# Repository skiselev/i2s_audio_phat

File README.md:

# I2S Audio pHAT
I2S Audio Interface for Raspberry Pi Zero

## Introduction
This is a Raspberry Pi Zero pHAT form-factor I2S audio interface board based on a [Cirrus Logic (Wolfson) WM8731](https://www.cirrus.com/products/wm8731/) audio codec. It provides line input, line output, headphones output, and includes an on-board microphone.

## Hardware Documentation

### Schematic and PCB Layout

[Schematic - Version 3.0](documentation/I2S_Audio_pHAT-Schematic-3.0.pdf)

[PCB Layout - Version 3.0](documentation/I2S_Audio_pHAT-Board-3.0.pdf)

### Bill of Materials

[I2S Audio pHAT project on Mouser.com](https://www.mouser.com/ProjectManager/ProjectDetail.aspx?AccessID=6262cdf84a) - View and order all components except of the PCB.

[I2S Audio pHAT project on OSH Park](https://oshpark.com/shared_projects/yxrgLBxI) - View and order the PCB.

Component type     | Reference | Description                       | Quantity | Possible sources and notes 
------------------ | --------- | --------------------------------- | -------- | --------------------------
PCB                |           | I2S Audio pHAT PCB - Version 3.0  | 1        | Order from [OSH Park](https://oshpark.com/shared_projects/yxrgLBxI)
Integrated Circuit | U1        | WM8731, I2S audio codec, SSOP28   | 1        | Mouser [238-WM8731SEDS/V](https://www.mouser.com/ProductDetail/238-WM8731SEDS-V)
Integrated Circuit | U2        | TPS79333DBVR, LDO, SOT23-5        | 1        | Mouser [595-TPS79333DBVR](https://www.mouser.com/ProductDetail/595-TPS79333DBVR)
Integrated Circuit | U3        | CAT24C32WI-GT3, I2C EEPROM, SOIC8 | 1        | Mouser [698-CAT24C32WI-GT3](https://www.mouser.com/ProductDetail/698-CAT24C32WI-GT3)
Crystal            | X1        | 12.288MHz, 3 mm x 5.3 mm          | 1        | Mouser [717-7A-12.288MAAJ-T](https://www.mouser.com/ProductDetail/717-7A-12288MAAJ-T)
Microphone         | MK1       | 9.7 mm, electret condenser microphone | 1        | Mouser [490-CMA-4544PF-W](https://www.mouser.com/ProductDetail/490-CMA-4544PF-W)
Connector          | P1        | 3.5 mm audio jack, blue           | 1        | Mouser [806-STX-31205B284C](https://www.mouser.com/ProductDetail/806-STX-31205B284C)
Connector          | P2        | 3.5 mm audio jack, green          | 1        | Mouser [806-STX-31205B577C](https://www.mouser.com/ProductDetail/806-STX-31205B577C)
Connector          | P3        | 3.5 mm audio jack, black          | 1        | Mouser [806-STX-3120-5B](https://www.mouser.com/ProductDetail/806-STX-3120-5B)
Connector          | P4        | 20x2, 2.54 mm, socket             | 1        | Mouser [517-929852-01-20-RB](https://www.mouser.com/ProductDetail/517-929852-01-20-RB)
Header             | JP1       | 2x1, 2.54mm, header               | 1        | (optional) Mouser [855-M20-9990245](https://www.mouser.com/ProductDetail/855-M20-9990245)
Capacitor          | C1, C2    | 22pF, 0603                        | 2        | Mouser [77-VJ0603A220JXACBC](https://www.mouser.com/ProductDetail/77-VJ0603A220JXACBC)
Capacitor          | C3-C5     | 220pF, 0603                       | 3        | Mouser [77-VJ0603A221GXAPBC](https://www.mouser.com/ProductDetail/77-VJ0603A221GXAPBC)
Capacitor          | C6        | 0.01uF, 0603                      | 1        | Mouser [77-VJ0603Y103KXACBC](https://www.mouser.com/ProductDetail/77-VJ0603Y103KXACBC)
Capacitor          | C7-C12    | 0.1uF, 0603                       | 6        | Mouser [77-VJ0603Y104JXJPBC](https://www.mouser.com/ProductDetail/77-VJ0603Y104JXJPBC)
Capacitor          | C13-C15   | 1uF, 5 mm, radial                 | 3        | Mouser [647-USW1H010MDD](https://www.mouser.com/ProductDetail/647-USW1H010MDD)
Capacitor          | C16, C17  | 10uF, 5 mm, radial                | 2        | Mouser [647-USW1H100MDD](https://www.mouser.com/ProductDetail/647-USW1H100MDD)
Capacitor          | C18-C21   | 10uF, 0603                        | 4        | Mouser [81-GRM188R61A106KE9D](https://www.mouser.com/ProductDetail/81-GRM188R61A106KE9D)
Capacitor          | C22, C23  | 220uF, 6.3 mm, radial             | 2        | Mouser [647-USW0J221MDD](https://www.mouser.com/ProductDetail/647-USW0J221MDD)
Resistor           | R1-R6     | 33 ohm, 0603                      | 6        | Mouser [603-RC0603FR-0733RL](https://www.mouser.com/ProductDetail/603-RC0603FR-0733RL)
Resistor           | R7, R8    | 100 ohm, 0603                     | 2        | Mouser [603-RC0603FR-07100RL](https://www.mouser.com/ProductDetail/603-RC0603FR-07100RL)
Resistor           | R9        | 330 ohm, 0603                     | 1        | Mouser [603-RC0603FR-07330RL](https://www.mouser.com/ProductDetail/603-RC0603FR-07330RL)
Resistor           | R10       | 680 ohm, 0603                     | 1        | Mouser [603-RC0603FR-07680RL](https://www.mouser.com/ProductDetail/603-RC0603FR-07680RL)
Resistor           | R11       | 1 kohm, 0603                      | 1        | Mouser [603-RC0603FR-071KL](https://www.mouser.com/ProductDetail/603-RC0603FR-071KL)
Resistor           | R12, R13  | 3.9 kohm, 0603                    | 2        | Mouser [603-RC0603FR-073K9L](https://www.mouser.com/ProductDetail/603-RC0603FR-073K9L)
Resistor           | R14-R18   | 5.6 kohm, 0603                    | 5        | Mouser [603-RC0603FR-075K6L](https://www.mouser.com/ProductDetail/603-RC0603FR-075K6L)
Resistor           | R19-R22   | 47 kohm, 0603                     | 4        | Mouser [603-RC0603FR-0747KL](https://www.mouser.com/ProductDetail/603-RC0603FR-0747KL)

## Software Documentation

### Raspbian Configuration

Open `/boot/config.txt` in your favorite editor (nano, vi) as root, for example:

    sudo nano /boot/config.txt

Comment out the `dtparam=audio=on` line:

    # Enable audio (loads snd_bcm2835)
    #dtparam=audio=on

When using I2S Audio pHAT _without_ ID EEPROM (see [Raspberry Pi HAT ID EEPROM Programming](#raspberry-pi-hat-id-eeprom-programming) section below), add the following lines:

    # Enable WM8731 codec
    dtparam=i2c_arm=on
    dtparam=i2s=on
    dtoverlay=i2s-mmap
    dtoverlay=rpi-proto

Save the file and reboot the system.

Start `alsamixer`. If the I2S Audio pHAT is detected properly, it should show _Card: snd_rpi_proto_ on the top left. Also use this opportunity to unmute *Output Mixer HiFi* control, otherwise the codec will not play any sound. To do so, use cursor keys to highlight that control, and then press the *M* key to unmute it.

When recording the sound, switch to *Capture* controls in `alsamixer` by pressing the *F4* key. Next select the capture source: *Line* or *Mic*, and unmute it by pressing the *Space* key.

Now you can use your favorite application to play music or record sound. Enjoy!

### Raspberry Pi HAT ID EEPROM Programming

The I2S Audio pHAT includes an ID EEPROM as specified by HAT requirements. This ID EEPROM allows Raspbian to automatically detect the I2S Audio pHAT, add it to the device tree, and load approprate overlays and kernel modules. Follow the instructions below to program the EEPROM.

Clone the Raspberry Pi [hats](https://github.com/raspberrypi/hats) repostory from GitHub:

    git clone https://github.com/raspberrypi/hats

Clone the [I2S Audio pHAT](https://github.com/skiselev/i2s_audio_phat) repository from GitHub:

    git clone https://github.com/skiselev/i2s_audio_phat

Build the `eepromutils` in the `hats` repository:

    cd hats/eepromutils
    make

Create the `i2s_audio_phat.eep` ID EEPROM image, using the `eeprom_settings_i2s_audio_phat.txt` file provided in the `i2s_audio_phat` repository:

    ./eepmake ../../i2s_audio_phat/eeprom_settings_i2s_audio_phat.txt i2s_audio_phat.eep /boot/overlays/rpi-proto.dtbo

Finally, flash the `i2s_audio_phat.eep` ID EEPROM image to the EEPROM. Make sure to close the JP1 jumper on the I2S Audio pHAT before writing the EEPROM, for example using male to male jumper wire, or otherwise the write will fail.

    sudo ./eepflash.sh -w -f=i2s_audio_phat.eep -t=24c32

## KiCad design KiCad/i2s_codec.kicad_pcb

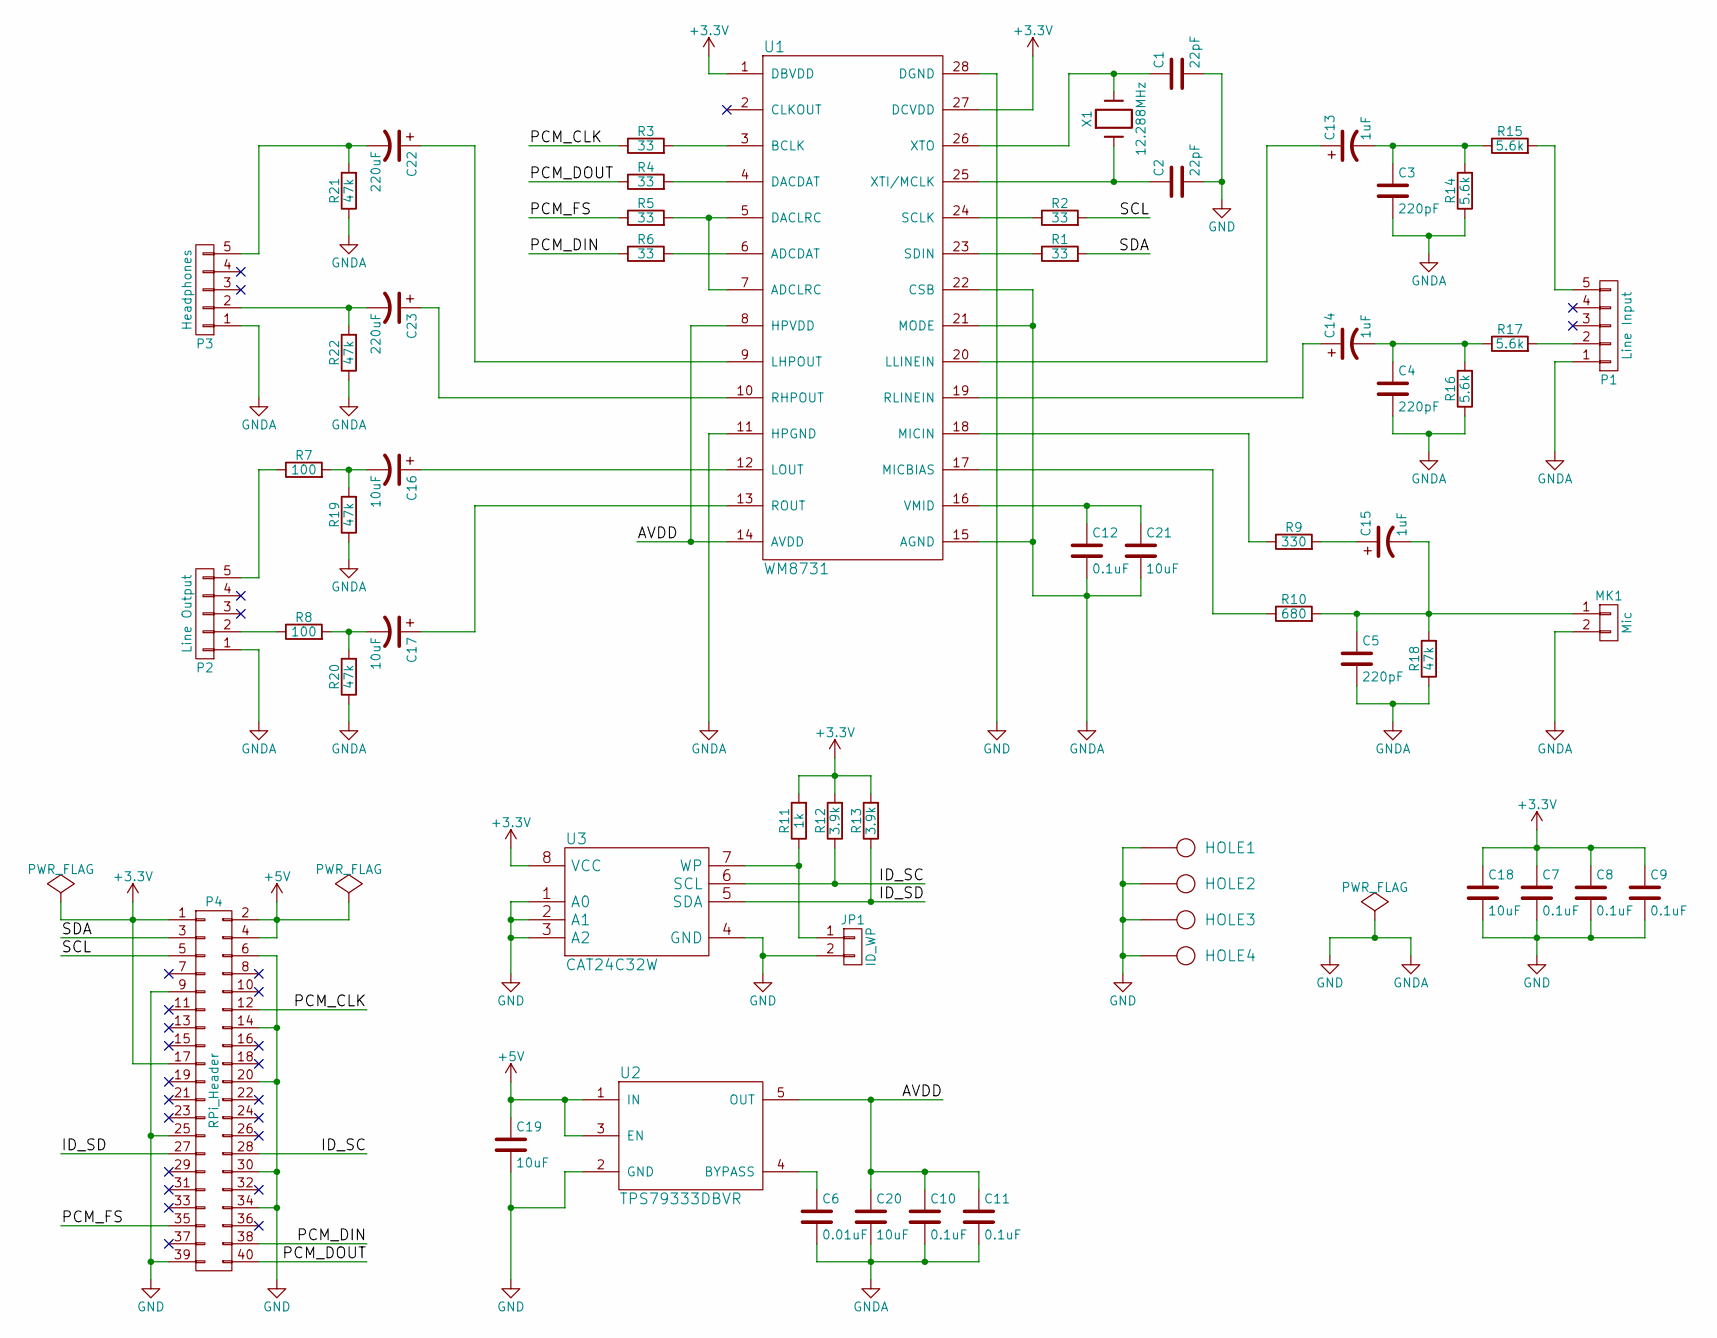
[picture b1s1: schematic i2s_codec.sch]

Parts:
C1, C2: 22pF; C_0603_HandSoldering
C3, C4, C5: 220pF; C_0603_HandSoldering
C6: 0.01uF; C_0603_HandSoldering
C7, C8, C9, C10, C11, C12: 0.1uF; C_0603_HandSoldering
C13, C14, C15: 1uF; Cap_Elec_Radial_5mm
C16, C17: 10uF; Cap_Elec_Radial_5mm
C18, C19, C20, C21: 10uF; C_0603_HandSoldering
C22, C23: 220uF; Cap_Elec_Radial_6.3mm
HOLE1, HOLE2, HOLE3, HOLE4: HOLE; Hole_2.75mm
JP1: ID_WP; Conn_Pin_Header_2x1_2.54mm_NoKey
MK1: Mic; Microphone
P1: Line Input; Conn_Audio_3.5mm_Stereo
P2: Line Output; Conn_Audio_3.5mm_Stereo
P3: Headphones; Conn_Audio_3.5mm_Stereo
P4: RPi_Header; Conn_Pin_Header_20x2_2.54mm
R1, R2, R3, R4, R5, R6: 33; R_0603_HandSoldering
R7, R8: 100; R_0603_HandSoldering
R9: 330; R_0603_HandSoldering
R10: 680; R_0603_HandSoldering
R11: 1k; R_0603_HandSoldering
R12, R13: 3.9k; R_0603_HandSoldering
R14, R15, R16, R17: 5.6k; R_0603_HandSoldering
R18, R19, R20, R21, R22: 47k; R_0603_HandSoldering
U1: WM8731; IC_SSOP28
U2: TPS79333DBVR; IC_SOT23-5_Hand_Soldering
U3: CAT24C32W; IC_SOIC8_Narrow
X1: 12.288MHz; Crystal_5.0x3.2mm

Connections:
+3V3: C7.1, C8.1, C9.1, C18.1, P4.1, P4.17, R11.2, R12.2, R13.2, U1.1 (DBVDD), U1.27 (DCVDD), U3.8 (VCC)
+5V: C19.1, P4.2, P4.4, U2.1 (IN), U2.3 (EN)
/AVDD: C10.1, C11.1, C20.1, U1.8 (HPVDD), U1.14 (AVDD), U2.5 (OUT)
/ID_SC: P4.28, R12.1, U3.6 (SCL)
/ID_SD: P4.27, R13.1, U3.5 (SDA)
/PCM_CLK: P4.12, R3.1
/PCM_DIN: P4.38, R6.1
/PCM_DOUT: P4.40, R4.1
/PCM_FS: P4.35, R5.1
/SCL: P4.5, R2.2
/SDA: P4.3, R1.2
GND: C1.2, C2.2, C3.2, C4.2, C5.2, C6.2, C7.2, C8.2, C9.2, C10.2, C11.2, C12.2, C18.2, C19.2, C20.2, C21.2, HOLE1.1, HOLE2.1, HOLE3.1, HOLE4.1, JP1.2, MK1.2, P1.1, P2.1, P3.1, P4.6, P4.9, P4.14, P4.20, P4.25, P4.30, P4.34, P4.39, R14.1, R16.1, R18.1, R19.1, R20.1, R21.1, R22.1, U1.11 (HPGND), U1.15 (AGND), U1.21 (MODE), U1.22 (CSB), U1.28 (DGND), U2.2 (GND), U3.1 (A0), U3.2 (A1), U3.3 (A2), U3.4 (GND)
unnamed: C1.1, U1.26 (XTO), X1.2
unnamed: C2.1, U1.25 (XTI/MCLK), X1.1
unnamed: C6.1, U2.4 (BYPASS)
unnamed: C12.1, C21.1, U1.16 (VMID)
unnamed: C13.1, U1.20 (LLINEIN)
unnamed: C3.1, C13.2, R14.2, R15.1
unnamed: C14.1, U1.19 (RLINEIN)
unnamed: C4.1, C14.2, R16.2, R17.1
unnamed: C15.1, R9.2
unnamed: C5.1, C15.2, MK1.1, R10.2, R18.2
unnamed: C16.1, U1.12 (LOUT)
unnamed: C16.2, R7.2, R19.2
unnamed: C17.1, U1.13 (ROUT)
unnamed: C17.2, R8.2, R20.2
unnamed: C22.1, U1.9 (LHPOUT)
unnamed: C22.2, P3.5, R21.2
unnamed: C23.1, U1.10 (RHPOUT)
unnamed: C23.2, P3.2, R22.2
unnamed: JP1.1, R11.1, U3.7 (WP)
unnamed: P1.2, R17.2
unnamed: P1.5, R15.2
unnamed: P2.2, R8.1
unnamed: P2.5, R7.1
unnamed: R1.1, U1.23 (SDIN)
unnamed: R2.1, U1.24 (SCLK)
unnamed: R3.2, U1.3 (BCLK)
unnamed: R4.2, U1.4 (DACDAT)
unnamed: R5.2, U1.5 (DACLRC), U1.7 (ADCLRC)
unnamed: R6.2, U1.6 (ADCDAT)
unnamed: R9.1, U1.18 (MICIN)
unnamed: R10.1, U1.17 (MICBIAS)

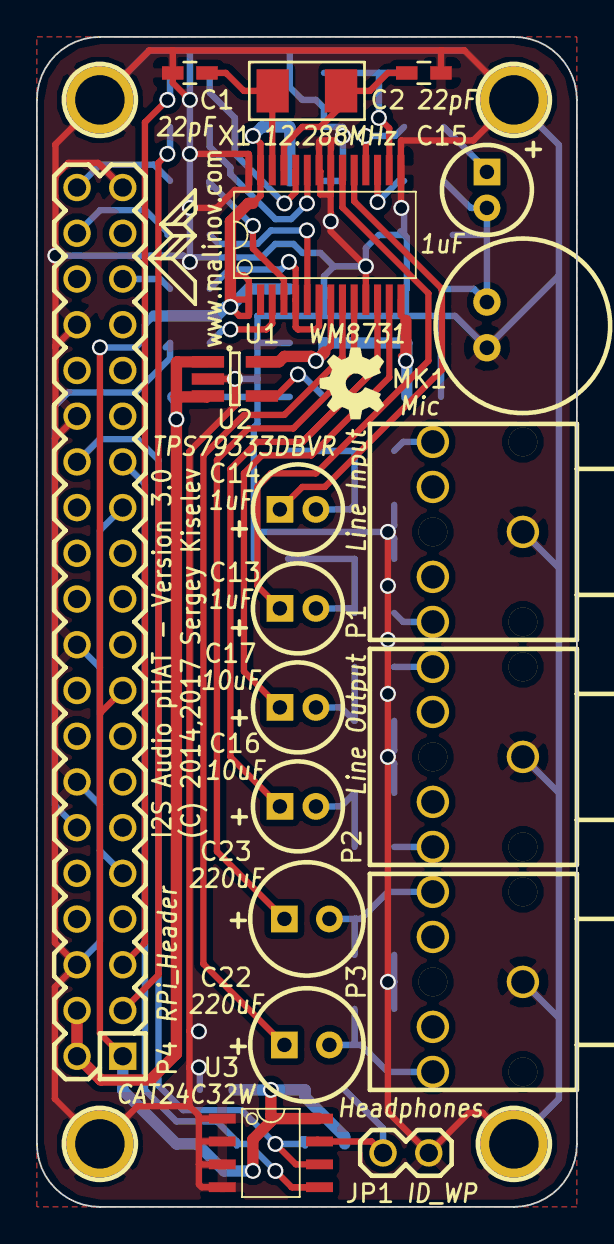
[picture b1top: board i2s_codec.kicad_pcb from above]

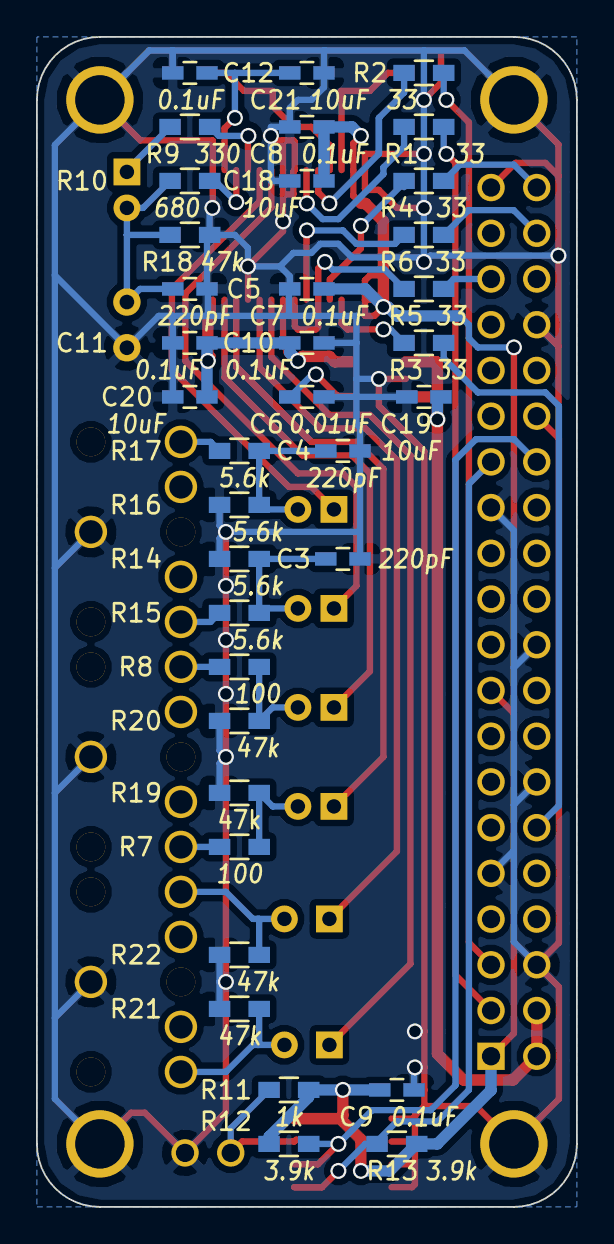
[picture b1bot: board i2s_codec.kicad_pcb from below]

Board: 2 copper layers, 30.0 x 65.0 mm, 59 parts (36 on the bottom side), 43 nets.

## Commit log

2017-09-06 Initial drop
2017-09-06 Move PDF files around and fix links in README.md
2017-09-07 Add top/bottom photos
2018-01-18 README.md: Update BoM: Audio electrolytic capacitors; shorter Mouser URLs
2018-01-18 README.md: Add ID EEPROM programming instructions
2018-01-18 README.md: Add sound recording notes
2018-01-18 README.md: Update the Raspbian configuration instructions
2018-01-18 eeprom_settings: Update product UUID
2018-01-18 README.md: Formatting
2018-01-18 README.md: Add links

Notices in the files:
KiCad/i2s_codec.kicad_pcb:
(C) 2014,2017 Sergey Kiselev
